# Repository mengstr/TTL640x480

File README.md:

# TTL640x480

I had been thinking for a while about making a TTL-based VGA video card when a post in the Z80-group on Facebook triggered me into action of actually realizing my design.

The ultimate goal is of course to make this circuit into a 80x25 character "video card" that uses only plain TTLs, a Character ROM and some RAM.  But as a start I decicded to focus on the counters for rows and columns as well as the generation of sync and blanking pulses.

There was at least one other implementation of this idea - the *Masochist's Video Card* by Pyroelectro but it used 30+ chips to basically do the sam thing as I wanted.

I went for a more minimalistic approach, while still maintaining full compliance with the 640x480 VGA standard.

I got it down to 3 counter ICs and 6 logic gates ICs for a total of 9 ICs, but I also use 3 diodes and a pulldown resistor as a discrete NOR (cheating a bit - so really it should be a total of 10 ICs to be fair) 

All of this was back in Januari 2019, and then in July 2019 the ever so excellent Ben Eater published his own version of "The world's worst video card" https://eater.net/vga.  He made it with 20 ICs. I must admit I'm secretly happy that he didn't beat my chip count, but on the other hand his goal was not to make the lowest chip count but rather to make something educational.

### Schematics

### Part list
 3	×	74HCT393 Dual 4-bit counters  
 2	×	74HCT00 Quad 2-input NAND  
 1	×	74HCT10 Triple 3-input NAND  
 2	×	74HCT20 Dual 4-input NAND  
 1	×	74HCT04 Hex inverter  
 3	×	1N4148 Diodes   
 1	×	2K2 Resistor  
 1	×	25.175 MHz clock generator  

### Links
- My project at hackaday.io - https://hackaday.io/project/163298-ttl640x480
- Masochist's Video Card - http://www.pyroelectro.com/projects/masochists_video_card/
- Ben Eater's project - https://eater.net/vga

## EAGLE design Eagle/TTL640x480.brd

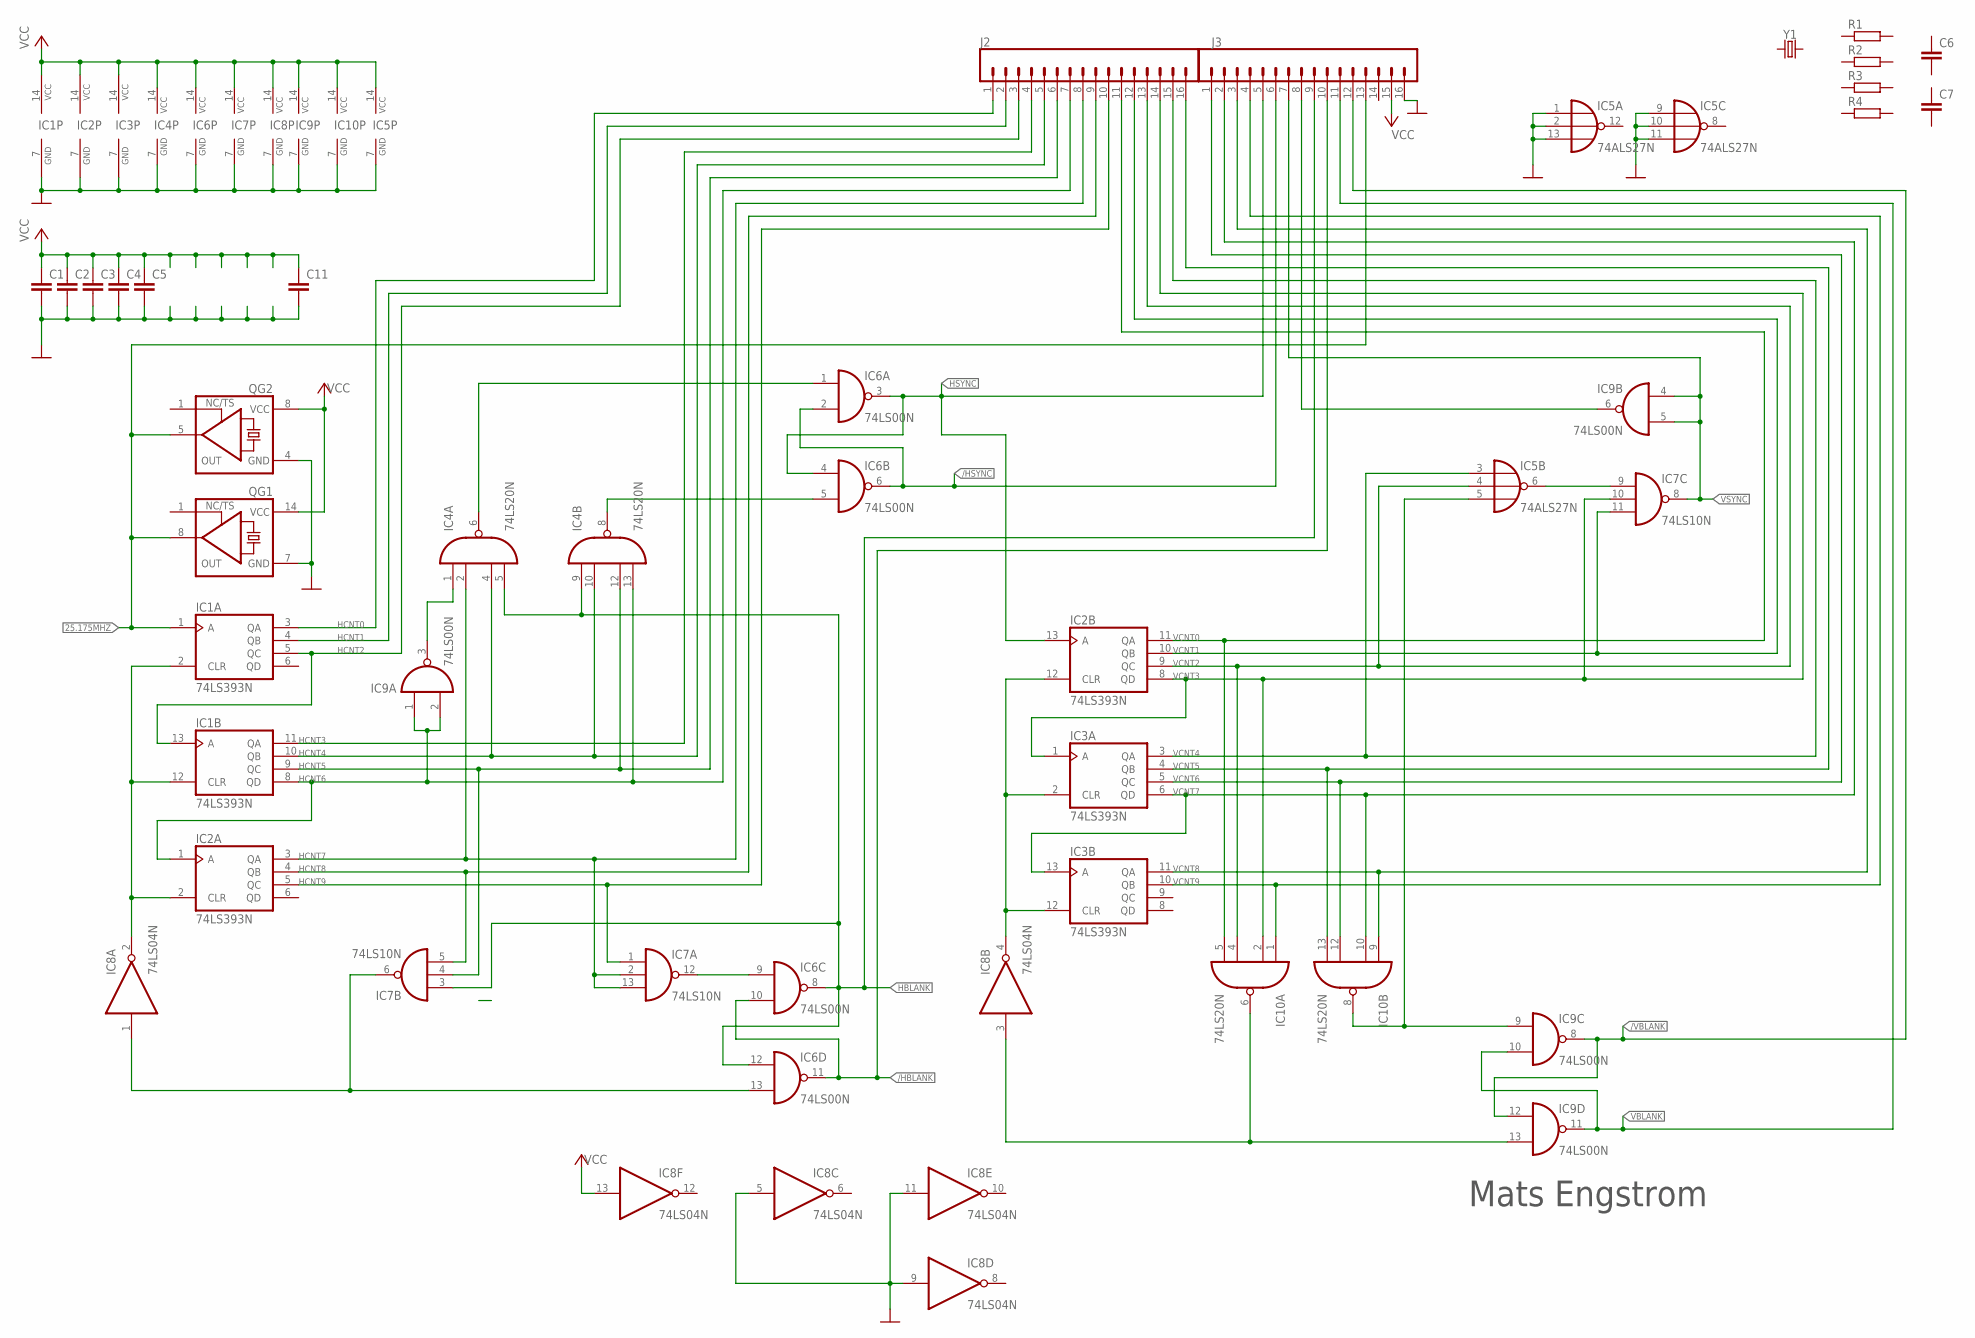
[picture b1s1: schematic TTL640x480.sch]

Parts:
C1, C2, C3, C4, C5, C6, C7, C11: C-EU050-024X044; C050-024X044
IC1, IC2, IC3: 74LS393N; DIL14
IC4, IC10: 74LS20N; DIL14
IC5: 74ALS27N; DIL14
IC6, IC9: 74LS00N; DIL14
IC7: 74LS10N; DIL14
IC8: 74LS04N; DIL14
J2, J3: CONN_16; 1X16
QG1: XO-14; DIL14S
QG2: XO-8; DIL08S
R1, R2, R3, R4: R-EU_0204/2V; 0204V
Y1: CRYSTALPTH-HC49US; HC49US

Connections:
25.175MHZ: IC1.1 (A), J3.13, QG1.8 (OUT), QG2.5 (OUT)
/HBLANK: IC6.10 (I1), IC6.11 (O), J3.10
/HSYNC: IC6.2 (I1), IC6.6 (O), J3.6
/VBLANK: IC9.8 (O), IC9.12 (I0), J3.12
GND: C1.2, C2.2, C3.2, C4.2, C5.2, C11.2, IC1.7 (GND), IC2.7 (GND), IC3.7 (GND), IC4.7 (GND), IC5.1 (I0), IC5.2 (I1), IC5.7 (GND), IC5.9 (I0), IC5.10 (I1), IC5.11 (I2), IC5.13 (I2), IC6.7 (GND), IC7.7 (GND), IC8.5 (I), IC8.7 (GND), IC8.9 (I), IC8.11 (I), IC9.7 (GND), IC10.7 (GND), J3.16, QG1.7 (GND), QG2.4 (GND)
HBLANK: IC4.5 (I3), IC4.9 (I0), IC6.8 (O), IC6.12 (I0), IC7.3 (I0), J3.9
HCNT0: IC1.3 (QA), J2.1
HCNT1: IC1.4 (QB), J2.2
HCNT2: IC1.5 (QC), IC1.13 (A), J2.3
HCNT3: IC1.11 (QA), J2.4
HCNT4: IC1.10 (QB), IC4.4 (I2), IC4.10 (I1), J2.5
HCNT5: IC1.9 (QC), IC4.12 (I2), IC7.4 (I1), J2.6
HCNT6: IC1.8 (QD), IC2.1 (A), IC4.13 (I3), IC9.1 (I0), IC9.2 (I1), J2.7
HCNT7: IC2.3 (QA), IC4.2 (I1), IC7.2 (I1), IC7.13 (I2), J2.8
HCNT8: IC2.4 (QB), IC7.5 (I2), J2.9
HCNT9: IC2.5 (QC), IC7.1 (I0), J2.10
HSYNC: IC2.13 (A), IC6.3 (O), IC6.4 (I0), J3.5
unnamed: IC9.6 (O), J3.8
unnamed: IC4.1 (I0), IC9.3 (O)
unnamed: IC1.2 (CLR), IC1.12 (CLR), IC2.2 (CLR), IC8.2 (O)
unnamed: IC5.5 (I2), IC9.9 (I0), IC10.8 (O)
unnamed: IC5.6 (O), IC7.9 (I0)
unnamed: IC2.12 (CLR), IC3.2 (CLR), IC3.12 (CLR), IC8.4 (O)
unnamed: IC8.3 (I), IC9.13 (I1), IC10.6 (O)
unnamed: IC4.6 (O), IC6.1 (I0)
unnamed: IC4.8 (O), IC6.5 (I1)
unnamed: IC6.9 (I0), IC7.12 (O)
unnamed: IC6.13 (I1), IC7.6 (O), IC8.1 (I)
VBLANK: IC9.10 (I1), IC9.11 (O), J3.11
VCC: C1.1, C2.1, C3.1, C4.1, C5.1, C11.1, IC1.14 (VCC), IC2.14 (VCC), IC3.14 (VCC), IC4.14 (VCC), IC5.14 (VCC), IC6.14 (VCC), IC7.14 (VCC), IC8.13 (I), IC8.14 (VCC), IC9.14 (VCC), IC10.14 (VCC), J3.15, QG1.14 (VCC), QG2.8 (VCC)
VCNT0: IC2.11 (QA), IC10.5 (I3), J2.11
VCNT1: IC2.10 (QB), IC7.11 (I2), J2.12
VCNT2: IC2.9 (QC), IC5.4 (I1), IC10.4 (I2), J2.13
VCNT3: IC2.8 (QD), IC3.1 (A), IC7.10 (I1), IC10.2 (I1), J2.14
VCNT4: IC3.3 (QA), IC5.3 (I0), J2.15
VCNT5: IC3.4 (QB), IC10.13 (I3), J2.16
VCNT6: IC3.5 (QC), IC10.12 (I2), J3.1
VCNT7: IC3.6 (QD), IC3.13 (A), IC10.10 (I1), J3.2
VCNT8: IC3.11 (QA), IC10.9 (I0), J3.3
VCNT9: IC3.10 (QB), IC10.1 (I0), J3.4
VSYNC: IC7.8 (O), IC9.4 (I0), IC9.5 (I1), J3.7

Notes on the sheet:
Mats Engstrom

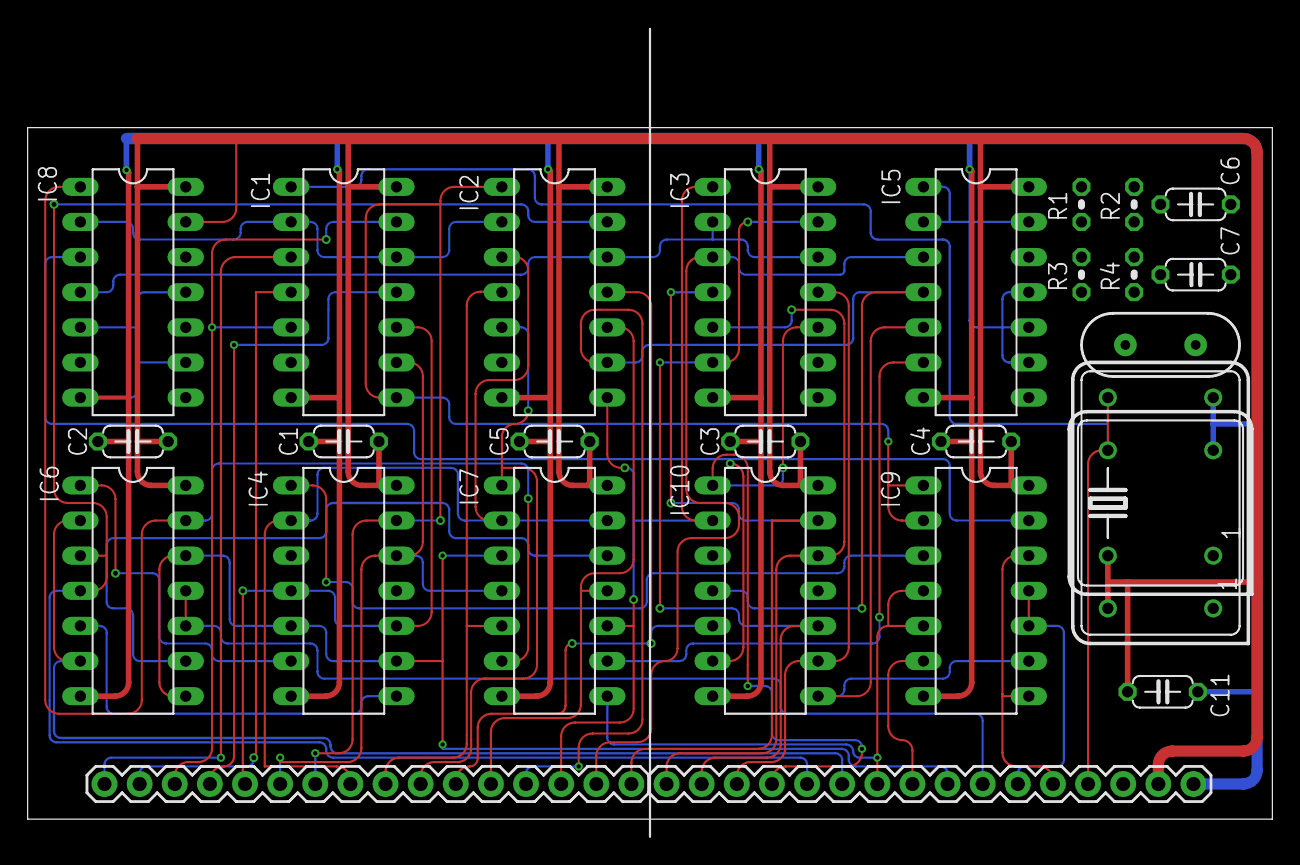
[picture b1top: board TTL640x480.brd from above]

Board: 2 copper layers, 89.8 x 58.4 mm, 27 parts (0 on the bottom side), 41 nets.

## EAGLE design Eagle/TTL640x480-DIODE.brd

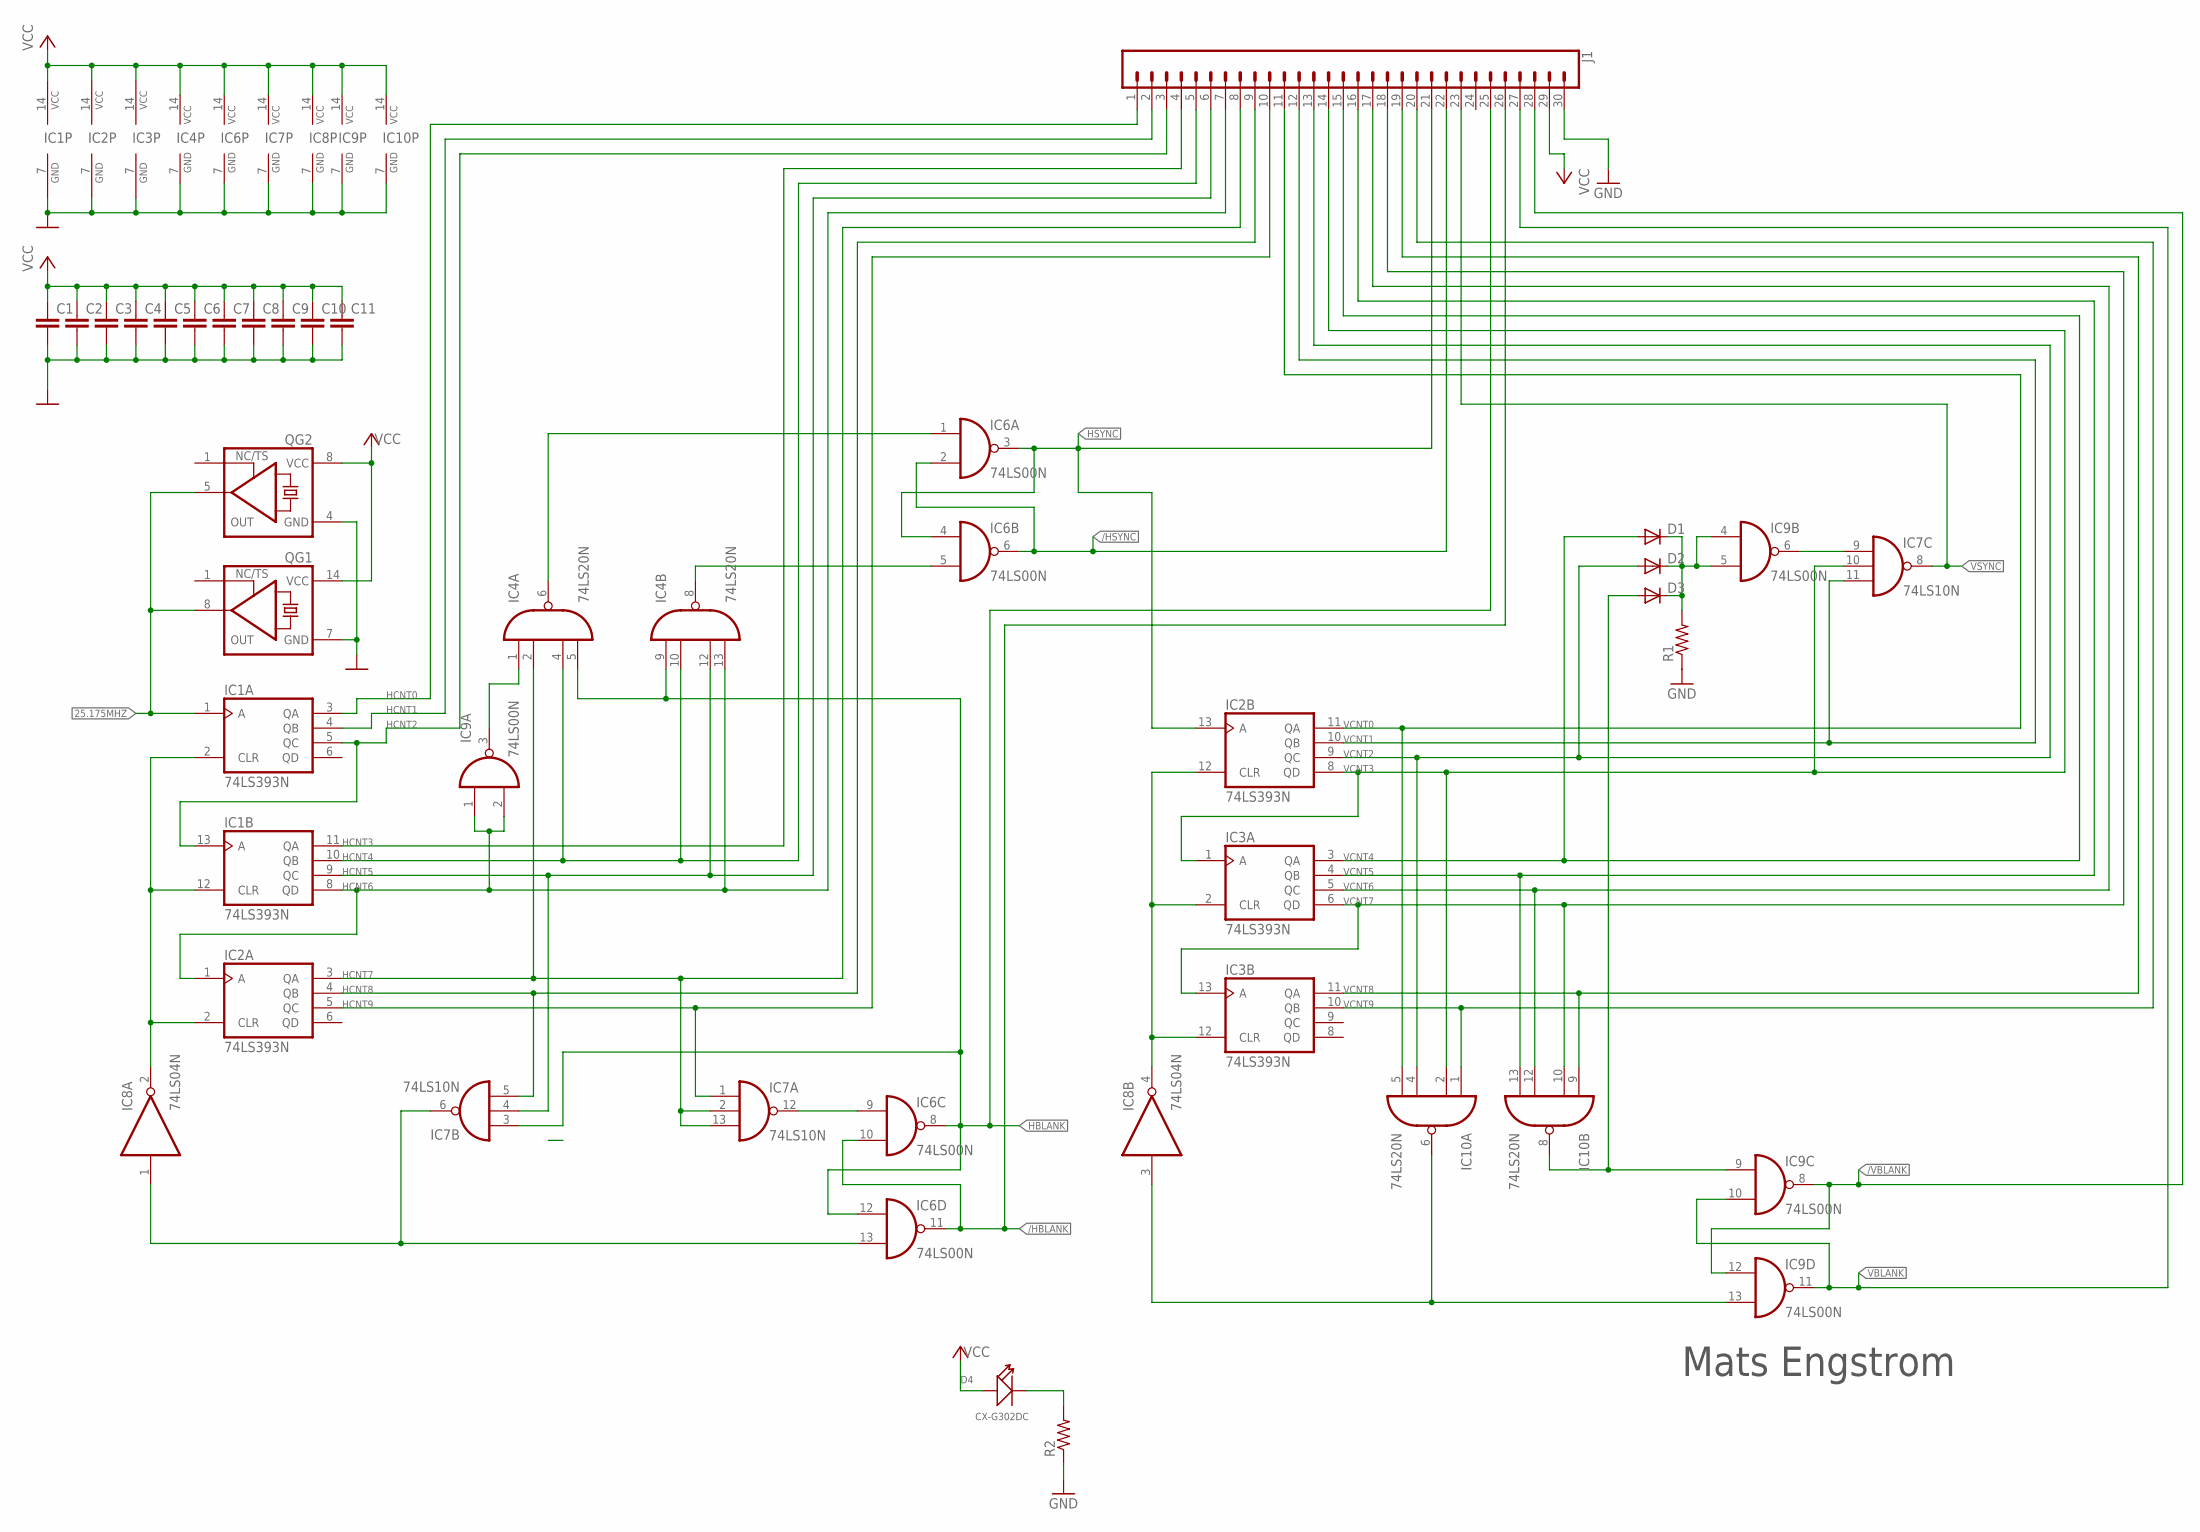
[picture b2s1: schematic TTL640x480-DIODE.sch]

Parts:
C1, C2, C3, C4, C5, C6, C7, C8, C9, C10, C11: C-EU050-024X044; C050-024X044
D1, D2, D3: 1N4148DO35-10; DO35-10
D4: CX-G302DC; LED2-2.54-D3.0MM
IC1, IC2, IC3: 74LS393N; DIL14
IC4, IC10: 74LS20N; DIL14
IC6, IC9: 74LS00N; DIL14
IC7: 74LS10N; DIL14
IC8: 74LS04N; DIL14
J1: CONN_30; 1X30
QG1: XO-14; DIL14S
QG2: XO-8; DIL08S
R1, R2: R-US_0204/7; 0204/7

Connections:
25.175MHZ: IC1.1 (A), QG1.8 (OUT), QG2.5 (OUT)
/HBLANK: IC6.10 (I1), IC6.11 (O), J1.26
/HSYNC: IC6.2 (I1), IC6.6 (O), J1.22
/VBLANK: IC9.8 (O), IC9.12 (I0), J1.28
GND: C1.2, C2.2, C3.2, C4.2, C5.2, C6.2, C7.2, C8.2, C9.2, C10.2, C11.2, IC1.7 (GND), IC2.7 (GND), IC3.7 (GND), IC4.7 (GND), IC6.7 (GND), IC7.7 (GND), IC8.7 (GND), IC9.7 (GND), IC10.7 (GND), J1.30, QG1.7 (GND), QG2.4 (GND), R1.1, R2.1
HBLANK: IC4.5 (I3), IC4.9 (I0), IC6.8 (O), IC6.12 (I0), IC7.3 (I0), J1.25
HCNT0: IC1.3 (QA), J1.1
HCNT1: IC1.4 (QB), J1.2
HCNT2: IC1.5 (QC), IC1.13 (A), J1.3
HCNT3: IC1.11 (QA), J1.4
HCNT4: IC1.10 (QB), IC4.4 (I2), IC4.10 (I1), J1.5
HCNT5: IC1.9 (QC), IC4.12 (I2), IC7.4 (I1), J1.6
HCNT6: IC1.8 (QD), IC2.1 (A), IC4.13 (I3), IC9.1 (I0), IC9.2 (I1), J1.7
HCNT7: IC2.3 (QA), IC4.2 (I1), IC7.2 (I1), IC7.13 (I2), J1.8
HCNT8: IC2.4 (QB), IC7.5 (I2), J1.9
HCNT9: IC2.5 (QC), IC7.1 (I0), J1.10
HSYNC: IC2.13 (A), IC6.3 (O), IC6.4 (I0), J1.21
unnamed: D1.C, D2.C, D3.C, IC9.4 (I0), IC9.5 (I1), R1.2
unnamed: IC4.1 (I0), IC9.3 (O)
unnamed: IC1.2 (CLR), IC1.12 (CLR), IC2.2 (CLR), IC8.2 (O)
unnamed: D3.A, IC9.9 (I0), IC10.8 (O)
unnamed: IC7.9 (I0), IC9.6 (O)
unnamed: IC2.12 (CLR), IC3.2 (CLR), IC3.12 (CLR), IC8.4 (O)
unnamed: IC8.3 (I), IC9.13 (I1), IC10.6 (O)
unnamed: D4.K (-), R2.2
unnamed: IC4.6 (O), IC6.1 (I0)
unnamed: IC4.8 (O), IC6.5 (I1)
unnamed: IC6.9 (I0), IC7.12 (O)
unnamed: IC6.13 (I1), IC7.6 (O), IC8.1 (I)
VBLANK: IC9.10 (I1), IC9.11 (O), J1.27
VCC: C1.1, C2.1, C3.1, C4.1, C5.1, C6.1, C7.1, C8.1, C9.1, C10.1, C11.1, D4.A (+), IC1.14 (VCC), IC2.14 (VCC), IC3.14 (VCC), IC4.14 (VCC), IC6.14 (VCC), IC7.14 (VCC), IC8.14 (VCC), IC9.14 (VCC), IC10.14 (VCC), J1.29, QG1.14 (VCC), QG2.8 (VCC)
VCNT0: IC2.11 (QA), IC10.5 (I3), J1.11
VCNT1: IC2.10 (QB), IC7.11 (I2), J1.12
VCNT2: D2.A, IC2.9 (QC), IC10.4 (I2), J1.13
VCNT3: IC2.8 (QD), IC3.1 (A), IC7.10 (I1), IC10.2 (I1), J1.14
VCNT4: D1.A, IC3.3 (QA), J1.15
VCNT5: IC3.4 (QB), IC10.13 (I3), J1.16
VCNT6: IC3.5 (QC), IC10.12 (I2), J1.17
VCNT7: IC3.6 (QD), IC3.13 (A), IC10.10 (I1), J1.18
VCNT8: IC3.11 (QA), IC10.9 (I0), J1.19
VCNT9: IC3.10 (QB), IC10.1 (I0), J1.20
VSYNC: IC7.8 (O), J1.23

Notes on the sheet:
Mats Engstrom

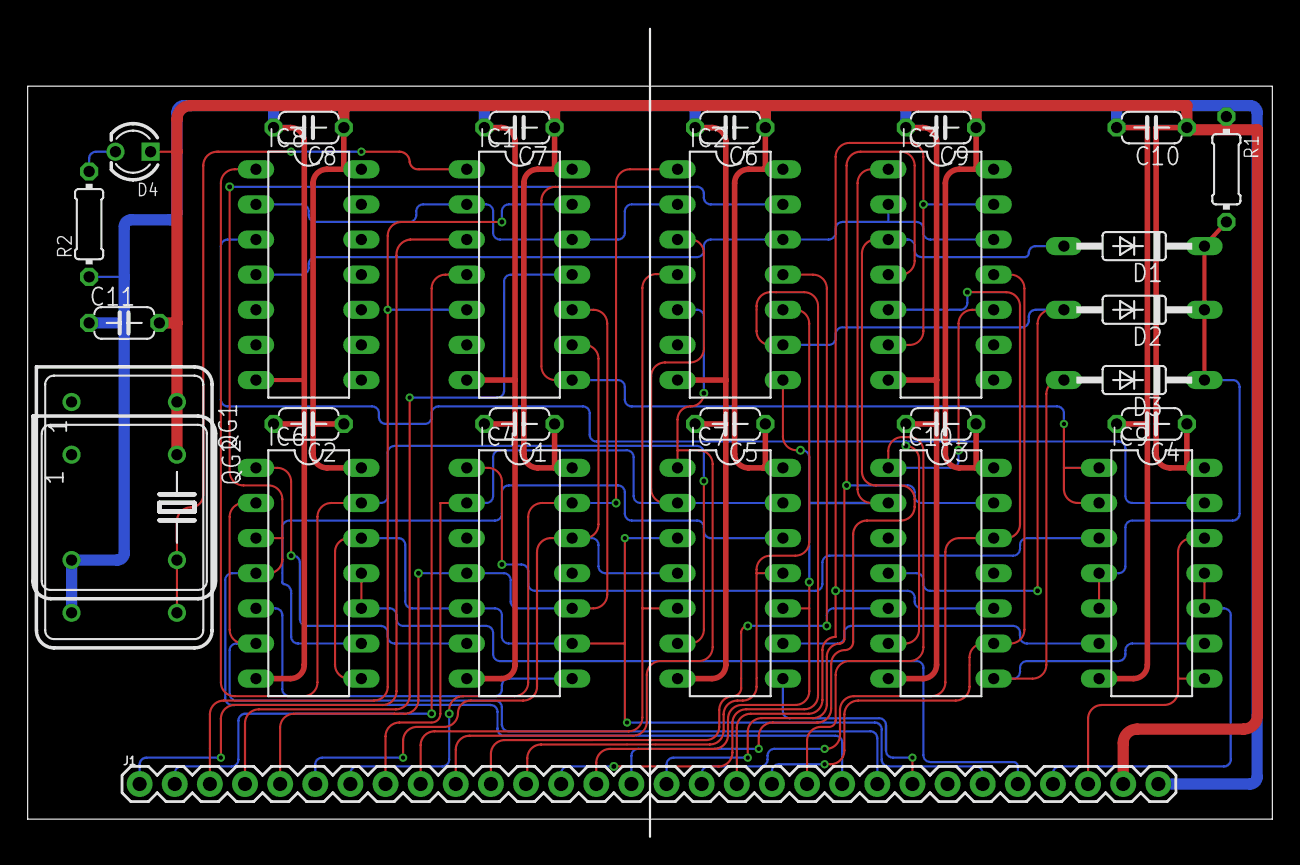
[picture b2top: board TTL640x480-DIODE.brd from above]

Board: 2 copper layers, 89.8 x 58.4 mm, 29 parts (0 on the bottom side), 42 nets.

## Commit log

2019-09-20 Add small image
2019-09-20 Test of design using Digital sim
2019-09-20 Add screenshot of Digital design

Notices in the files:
parts and their libraries:
SparkFun-Connectors: Licensing: Creative Commons ShareAlike 4.0 International - https://creativecommons.org/licenses/by-sa/4.0
